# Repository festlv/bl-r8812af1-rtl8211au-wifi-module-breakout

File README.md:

# BL-R8812AF1 (RTL8211AU) module breakout

Features:
* 5..18V power input
* JST GH for USB/power
* 12pin FFC connector (pinout for IVG-G3S / GK7205V210+IMX307) camera module- USB, microSD slot (optionally: power)

Current state:
* Power input tested and working fine at 5 and 12V
* WiFi module works
* FFC connection untested

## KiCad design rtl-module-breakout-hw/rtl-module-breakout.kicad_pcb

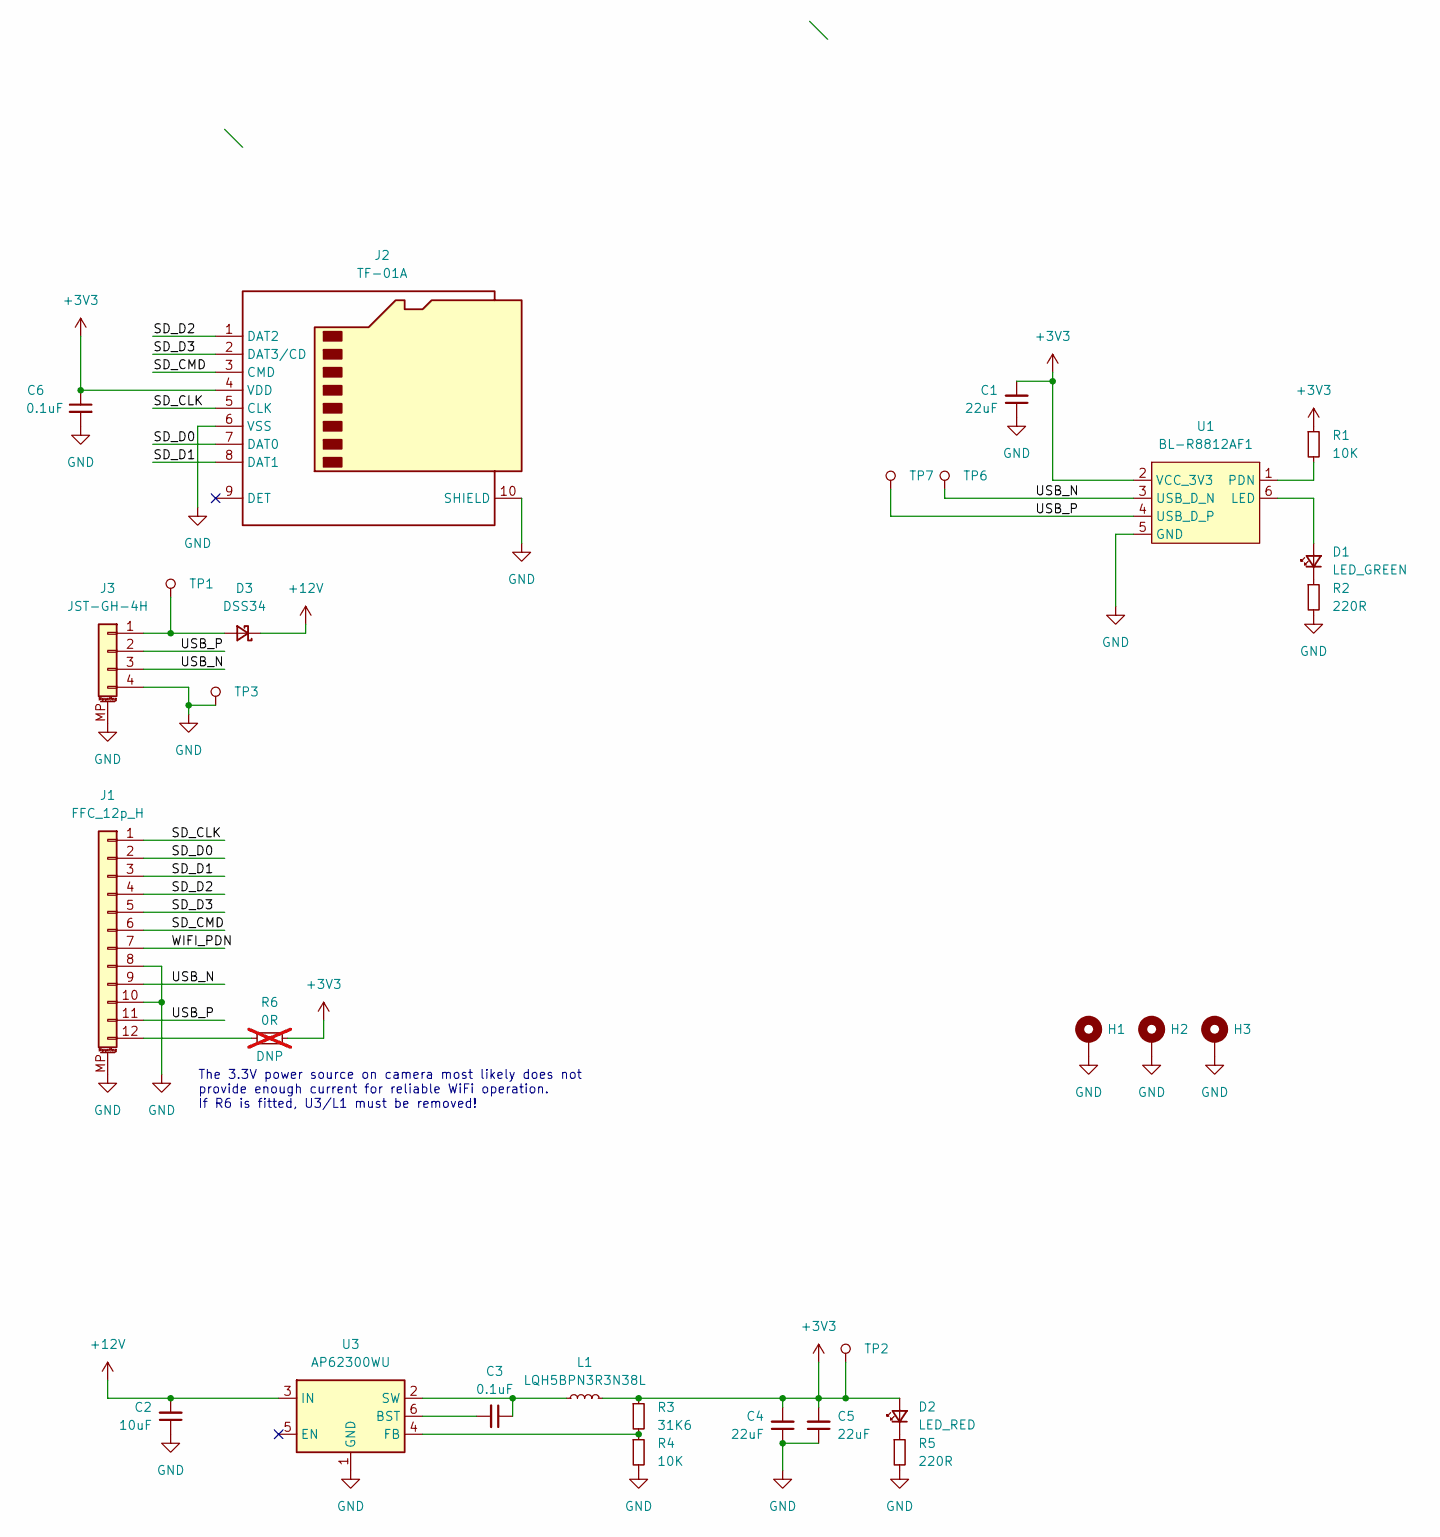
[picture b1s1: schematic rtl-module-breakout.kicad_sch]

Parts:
C1, C4, C5: 22uF; C_0805_2012Metric; LCSC# C380338
C2: 10uF; C_0805_2012Metric; LCSC# C15850
C3, C6: 0.1uF; C_0603_1608Metric
D1: LED_GREEN; LED_0603_1608Metric; MPN SZYY0603YG; LCSC# C434423
D2: LED_RED; LED_0603_1608Metric; MPN SZYY0603R; LCSC# C434419
D3: DSS34; D_SOD-123F; MPN DSS34; LCSC# C511866
H1, H2, H3: MH_2.2mm; MountingHole_2.2mm_M2_Pad_Via
J1: FFC_12p_H; Hirose_FH12-12S-0.5SH_1x12-1MP_P0.50mm_Horizontal; MPN AFC24-S12FIC-00; LCSC# C262290
J2: TF-01A; MPN TF-01A; LCSC# C91145
J3: JST-GH-4H; JST_GH_SM04B-GHS-TB_1x04-1MP_P1.25mm_Horizontal; MPN SM04B-GHS-TB; LCSC# C388709
L1: LQH5BPN3R3N38L; L_Sunlord_SWPA5020S; MPN LQH5BPN3R3N38L; LCSC# C703751
R1, R4: 10K; R_0603_1608Metric
R2, R5: 220R; R_0603_1608Metric; LCSC# C22962
R3: 31K6; R_0603_1608Metric; MPN 0603WAF3162T5E; LCSC# C25967
R6: 0R; R_0603_1608Metric; not fitted
TP1, TP2, TP3, TP6, TP7: TP_1MM; TestPoint_Pad_D1.0mm
U1: BL-R8812AF1; MPN BL-R8812AF1
U3: AP62300WU; TSOT-23-6; MPN AP62300WU-7; LCSC# C1880390

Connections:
+3V3: C1.2, C4.2, C5.2, C6.1, D2.2 (A), J2.4 (VDD), L1.2, R1.1, R3.1, R6.2, TP2.1, U1.2 (VCC_3V3)
+12V: C2.2, D3.1 (K), U3.3 (IN)
/SD_CLK: J1.1, J2.5 (CLK)
/SD_CMD: J1.6, J2.3 (CMD)
/SD_D0: J1.2, J2.7 (DAT0)
/SD_D1: J1.3, J2.8 (DAT1)
/SD_D2: J1.4, J2.1 (DAT2)
/SD_D3: J1.5, J2.2 (DAT3/CD)
/USB_N: J1.9, J3.3, TP6.1, U1.3 (USB_D_N)
/USB_P: J1.11, J3.2, TP7.1, U1.4 (USB_D_P)
/WIFI_PDN: J1.7
GND: C1.1, C2.1, C4.1, C5.1, C6.2, H1.1, H2.1, H3.1, J1.8, J1.10, J1.MP (MountPin), J2.6 (VSS), J2.10 (SHIELD), J3.4, J3.MP (MountPin), R2.2, R4.2, R5.2, TP3.1, U1.5 (GND), U1.7 (GND), U1.9 (GND), U1.10 (GND), U1.12 (GND), U3.1 (GND)
unnamed: D1.2 (A), U1.6 (LED)
unnamed: D1.1 (K), R2.1
unnamed: D2.1 (K), R5.1
unnamed: D3.2 (A), J3.1, TP1.1
unnamed: J1.12, R6.1
unnamed: R1.2, U1.1 (PDN)
unnamed: C3.2, U3.6 (BST)
unnamed: R3.2, R4.1, U3.4 (FB)
unnamed: C3.1, L1.1, U3.2 (SW)

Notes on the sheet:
The 3.3V power source on camera most likely does not provide enough current for reliable WiFi operation. If R6 is fitted, U3/L1 must be removed!

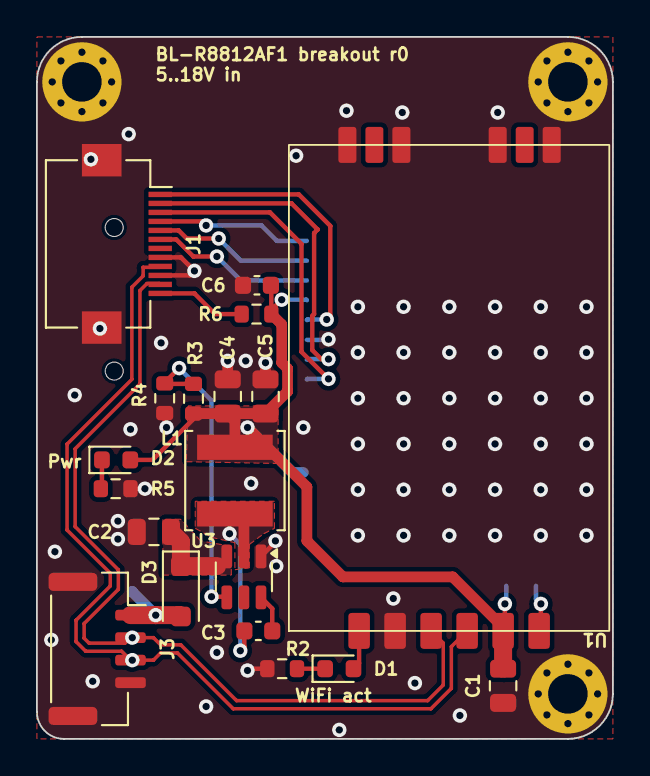
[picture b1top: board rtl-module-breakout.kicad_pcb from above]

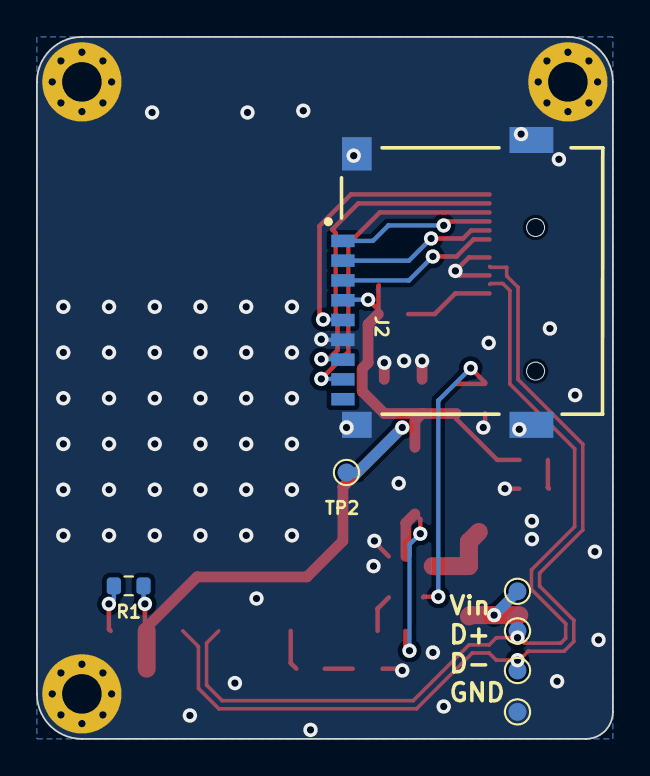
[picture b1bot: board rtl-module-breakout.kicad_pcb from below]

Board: 2 copper layers, 32.0 x 39.0 mm, 29 parts (7 on the bottom side), 20 nets.

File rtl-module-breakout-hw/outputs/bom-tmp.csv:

Item,Qty,Reference(s),Value,LibPart,Footprint,Datasheet,DNP,AltMPN,AltManufacturer,Config,LCSC#,MPN,Manufacturer
1,3,"C1, C4, C5",22uF,Device:C_Small,Capacitor_SMD:C_0805_2012Metric,~,,,,,C380338,,
2,1,C2,10uF,Device:C_Small,Capacitor_SMD:C_0805_2012Metric,~,,,,,C15850,,
3,2,"C3, C6",0.1uF,Device:C_Small,Capacitor_SMD:C_0603_1608Metric,~,,,,,,,
4,1,D1,LED_GREEN,hadv-ui:LED_GREEN,LED_SMD:LED_0603_1608Metric,~,,,,,C434423,SZYY0603YG,Yongyu Photoelectric
5,1,D2,LED_RED,hadv-ui:LED_RED,LED_SMD:LED_0603_1608Metric,~,,,,,C434419,SZYY0603R,Yongyu Photoelectric
6,1,D3,DSS34,hadv-diodes:DSS34,Diode_SMD:D_SOD-123F,https://datasheet.lcsc.com/lcsc/2004141809_BORN-DSS34_C511866.pdf,,,,,C511866,DSS34,BORN
7,1,J1,FFC_12p_H,hadv-connectors:FFC_12p_H,Connector_FFC-FPC:Hirose_FH12-12S-0.5SH_1x12-1MP_P0.50mm_Horizontal,~,,,,,C262290,AFC24-S12FIC-00,JUSHUO
8,1,J2,TF-01A,hadv-connectors:TF-01A,hadv-connectors:TF-01A,https://datasheet.lcsc.com/lcsc/1811082127_Korean-Hroparts-E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,,,,,C91145,TF-01A,Korean Hroparts
9,1,J3,JST-GH-4H,hadv-connectors:JST-GH-4H,Connector_JST:JST_GH_SM04B-GHS-TB_1x04-1MP_P1.25mm_Horizontal,~,,X1251WRS-04HF-LPSW,XKB,,C388709,SM04B-GHS-TB,JST
10,1,L1,LQH5BPN3R3N38L,hadv-inductors:LQH5BPN3R3N38L,Inductor_SMD:L_Sunlord_SWPA5020S,~,,,,,C703751,LQH5BPN3R3N38L,Murata
11,2,"R1, R4",10K,Device:R_Small,Resistor_SMD:R_0603_1608Metric,~,,,,,,,
12,2,"R2, R5",220R,Device:R_Small,Resistor_SMD:R_0603_1608Metric,~,,,,,C22962,,
13,1,R3,31K6,Device:R_Small,Resistor_SMD:R_0603_1608Metric,~,,,,,C25967,0603WAF3162T5E,
14,1,R6,0R,Device:R_Small,Resistor_SMD:R_0603_1608Metric,~,DNP,,,DNP,,,
15,1,U1,~,hadv-rf:BL-R8812AF1,hadv-rf:BL-R8812AF1,,,,,,,BL-R8812AF1,Unknown
16,1,U3,AP62300WU,hadv-vregs:AP62300WU,Package_TO_SOT_SMD:TSOT-23-6,https://www.diodes.com/assets/Datasheets/AP62300_AP62301_AP6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,,,,,C1880390,AP62300WU-7,Diodes Inc

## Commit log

2024-03-24 Initial revision
2024-03-24 Add outputs
